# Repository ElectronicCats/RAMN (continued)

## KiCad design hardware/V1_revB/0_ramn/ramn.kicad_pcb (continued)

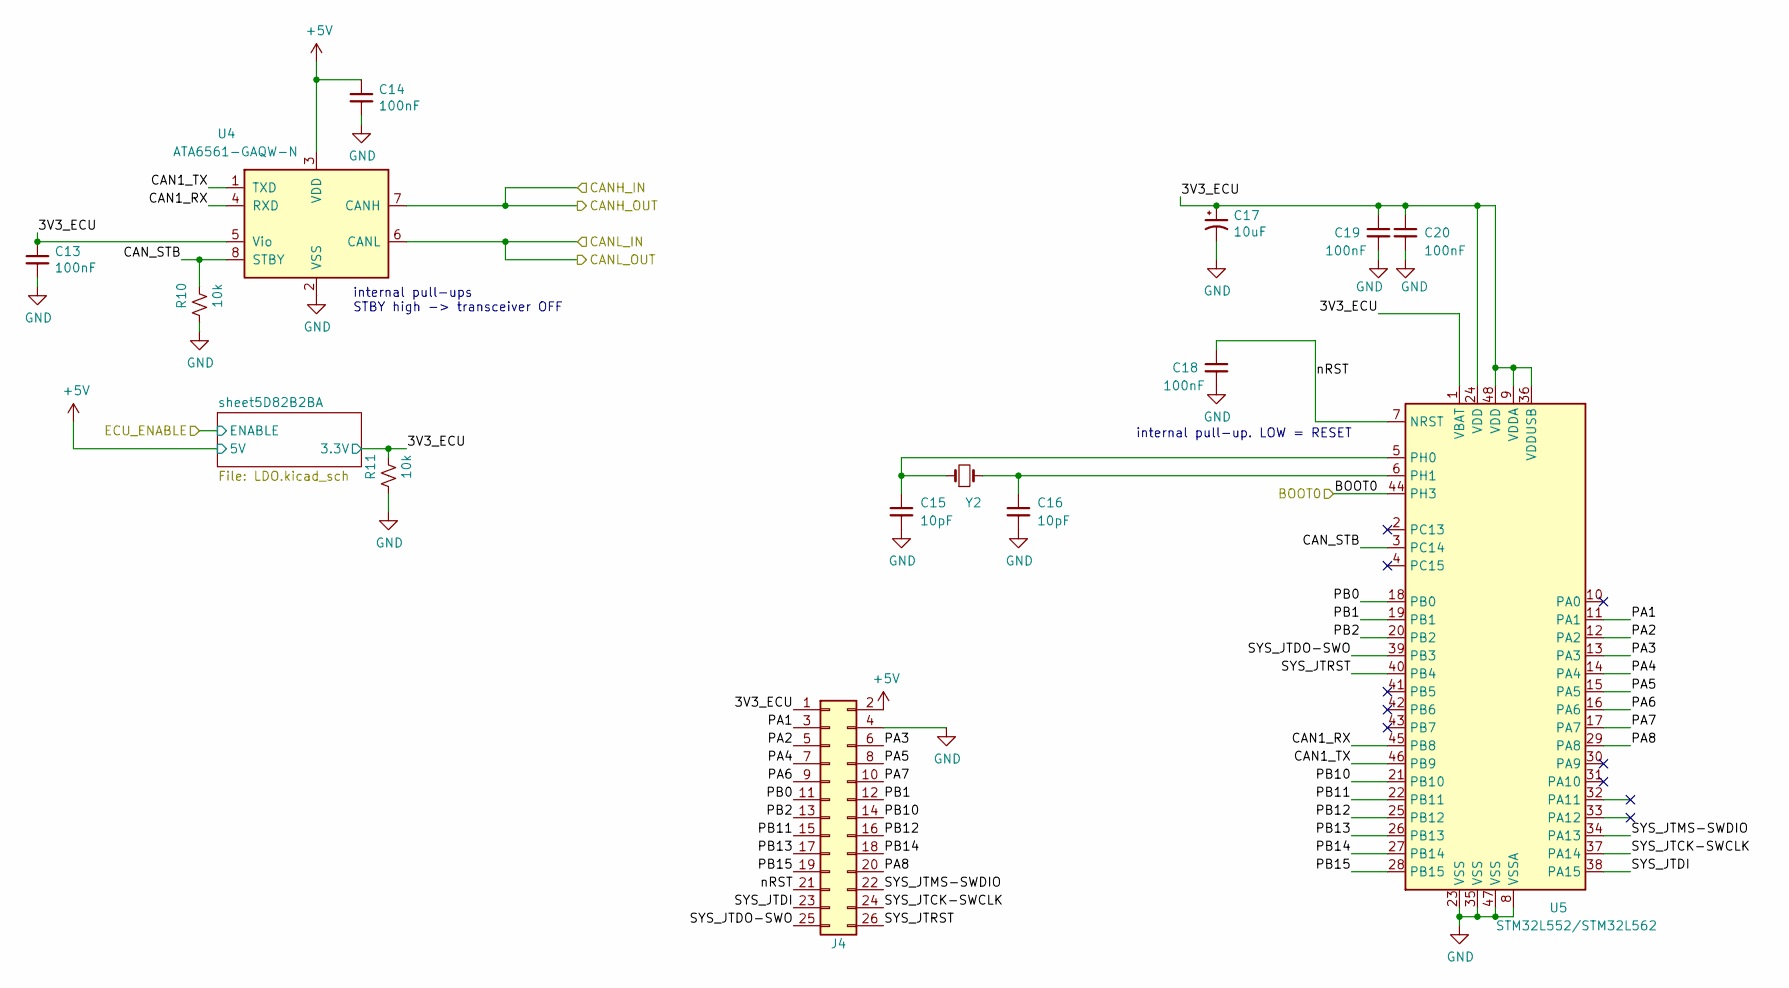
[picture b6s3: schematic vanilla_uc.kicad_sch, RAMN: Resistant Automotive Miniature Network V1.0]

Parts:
C13, C14, C18, C19, C20: 100nF; C_0603_1608Metric; lcsc# C599645
C15, C16: 10pF; C_0603_1608Metric; lcsc# C9807
C17: 10uF; C_1206_3216Metric; lcsc# C1848
J4: PinSocket_2x13_P2.54mm_Vertical; lcsc# C2897414
R10, R11: 10k; R_0603_1608Metric; lcsc# C98220
U4: ATA6561-GAQW-N; SOIC-8_3.9x4.9mm_P1.27mm; lcsc# C124015
U5: STM32L552/STM32L562; LQFP-48_7x7mm_P0.5mm; lcsc# C2969980
Y2: NX3225GD-8MHZ-STD-CRA-3; SMD-2_3.2x2.5mm; lcsc# C889706

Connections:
+5V: C14.1, J4.2, U4.3 (VDD); also elsewhere on the board
/ECUB/3V3_ECU: C13.1, C17.1, C19.1, C20.1, J4.1, R11.1, U4.5 (Vio), U5.1 (VBAT), U5.9 (VDDA), U5.24 (VDD), U5.36 (VDDUSB), U5.48 (VDD); also elsewhere on the board
/ECUB/BOOT0: U5.44 (PH3); also elsewhere on the board
/ECUB/CAN1_RX: U4.4 (RXD), U5.45 (PB8)
/ECUB/CAN1_TX: U4.1 (TXD), U5.46 (PB9)
/ECUB/CANH_IN: U4.7 (CANH); also elsewhere on the board
/ECUB/CANL_IN: U4.6 (CANL); also elsewhere on the board
/ECUB/CAN_STB: R10.1, U4.8 (STBY), U5.3 (PC14)
/ECUB/PA1: J4.3, U5.11 (PA1)
/ECUB/PA2: J4.5, U5.12 (PA2)
/ECUB/PA3: J4.6, U5.13 (PA3)
/ECUB/PA4: J4.7, U5.14 (PA4)
/ECUB/PA5: J4.8, U5.15 (PA5)
/ECUB/PA6: J4.9, U5.16 (PA6)
/ECUB/PA7: J4.10, U5.17 (PA7)
/ECUB/PA8: J4.20, U5.29 (PA8)
/ECUB/PB0: J4.11, U5.18 (PB0)
/ECUB/PB1: J4.12, U5.19 (PB1)
/ECUB/PB2: J4.13, U5.20 (PB2)
/ECUB/PB10: J4.14, U5.21 (PB10)
/ECUB/PB11: J4.15, U5.22 (PB11)
/ECUB/PB12: J4.16, U5.25 (PB12)
/ECUB/PB13: J4.17, U5.26 (PB13)
/ECUB/PB14: J4.18, U5.27 (PB14)
/ECUB/PB15: J4.19, U5.28 (PB15)
/ECUB/SYS_JTCK-SWCLK: J4.24, U5.37 (PA14)
/ECUB/SYS_JTDI: J4.23, U5.38 (PA15)
/ECUB/SYS_JTDO-SWO: J4.25, U5.39 (PB3)
/ECUB/SYS_JTMS-SWDIO: J4.22, U5.34 (PA13)
/ECUB/SYS_JTRST: J4.26, U5.40 (PB4)
/ECUB/nRST: C18.1, J4.21, U5.7 (NRST)
GND: C13.2, C14.2, C15.2, C16.2, C17.2, C18.2, C19.2, C20.2, J4.4, R10.2, R11.2, U4.2 (VSS), U5.8 (VSSA), U5.23 (VSS), U5.35 (VSS), U5.47 (VSS); also elsewhere on the board
unnamed: C15.1, U5.5 (PH0), Y2.1
unnamed: C16.1, U5.6 (PH1), Y2.2

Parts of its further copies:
C23, C24, C28, C29, C30: 100nF; C_0603_1608Metric; lcsc# C599645
C25, C26: 10pF; C_0603_1608Metric; lcsc# C9807
C27: 10uF; C_1206_3216Metric; lcsc# C1848
J5: PinSocket_2x13_P2.54mm_Vertical; lcsc# C2897414
R12, R13: 10k; R_0603_1608Metric; lcsc# C98220
U7: ATA6561-GAQW-N; SOIC-8_3.9x4.9mm_P1.27mm; lcsc# C124015
U8: STM32L552/STM32L562; LQFP-48_7x7mm_P0.5mm; lcsc# C2969980
Y3: NX3225GD-8MHZ-STD-CRA-3; SMD-2_3.2x2.5mm; lcsc# C889706

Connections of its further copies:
+5V: C24.1, J5.2, U7.3 (VDD); also elsewhere on the board
/ECUB/CANH_IN: U7.7 (CANH); also elsewhere on the board
/ECUB/CANL_IN: U7.6 (CANL); also elsewhere on the board
/ECUC/3V3_ECU: C23.1, C27.1, C29.1, C30.1, J5.1, R13.1, U7.5 (Vio), U8.1 (VBAT), U8.9 (VDDA), U8.24 (VDD), U8.36 (VDDUSB), U8.48 (VDD); also elsewhere on the board
/ECUC/BOOT0: U8.44 (PH3); also elsewhere on the board
/ECUC/CAN1_RX: U7.4 (RXD), U8.45 (PB8)
/ECUC/CAN1_TX: U7.1 (TXD), U8.46 (PB9)
/ECUC/CAN_STB: R12.1, U7.8 (STBY), U8.3 (PC14)
/ECUC/PA1: J5.3, U8.11 (PA1)
/ECUC/PA2: J5.5, U8.12 (PA2)
/ECUC/PA3: J5.6, U8.13 (PA3)
/ECUC/PA4: J5.7, U8.14 (PA4)
/ECUC/PA5: J5.8, U8.15 (PA5)
/ECUC/PA6: J5.9, U8.16 (PA6)
/ECUC/PA7: J5.10, U8.17 (PA7)
/ECUC/PA8: J5.20, U8.29 (PA8)
/ECUC/PB0: J5.11, U8.18 (PB0)
/ECUC/PB1: J5.12, U8.19 (PB1)
/ECUC/PB2: J5.13, U8.20 (PB2)
/ECUC/PB10: J5.14, U8.21 (PB10)
/ECUC/PB11: J5.15, U8.22 (PB11)
/ECUC/PB12: J5.16, U8.25 (PB12)
/ECUC/PB13: J5.17, U8.26 (PB13)
/ECUC/PB14: J5.18, U8.27 (PB14)
/ECUC/PB15: J5.19, U8.28 (PB15)
/ECUC/SYS_JTCK-SWCLK: J5.24, U8.37 (PA14)
/ECUC/SYS_JTDI: J5.23, U8.38 (PA15)
/ECUC/SYS_JTDO-SWO: J5.25, U8.39 (PB3)
/ECUC/SYS_JTMS-SWDIO: J5.22, U8.34 (PA13)
/ECUC/SYS_JTRST: J5.26, U8.40 (PB4)
/ECUC/nRST: C28.1, J5.21, U8.7 (NRST)
GND: C23.2, C24.2, C25.2, C26.2, C27.2, C28.2, C29.2, C30.2, J5.4, R12.2, R13.2, U7.2 (VSS), U8.8 (VSSA), U8.23 (VSS), U8.35 (VSS), U8.47 (VSS); also elsewhere on the board
unnamed: C25.1, U8.5 (PH0), Y3.1
unnamed: C26.1, U8.6 (PH1), Y3.2

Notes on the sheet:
internal pull-up. LOW = RESET
internal pull-ups STBY high -> transceiver OFF

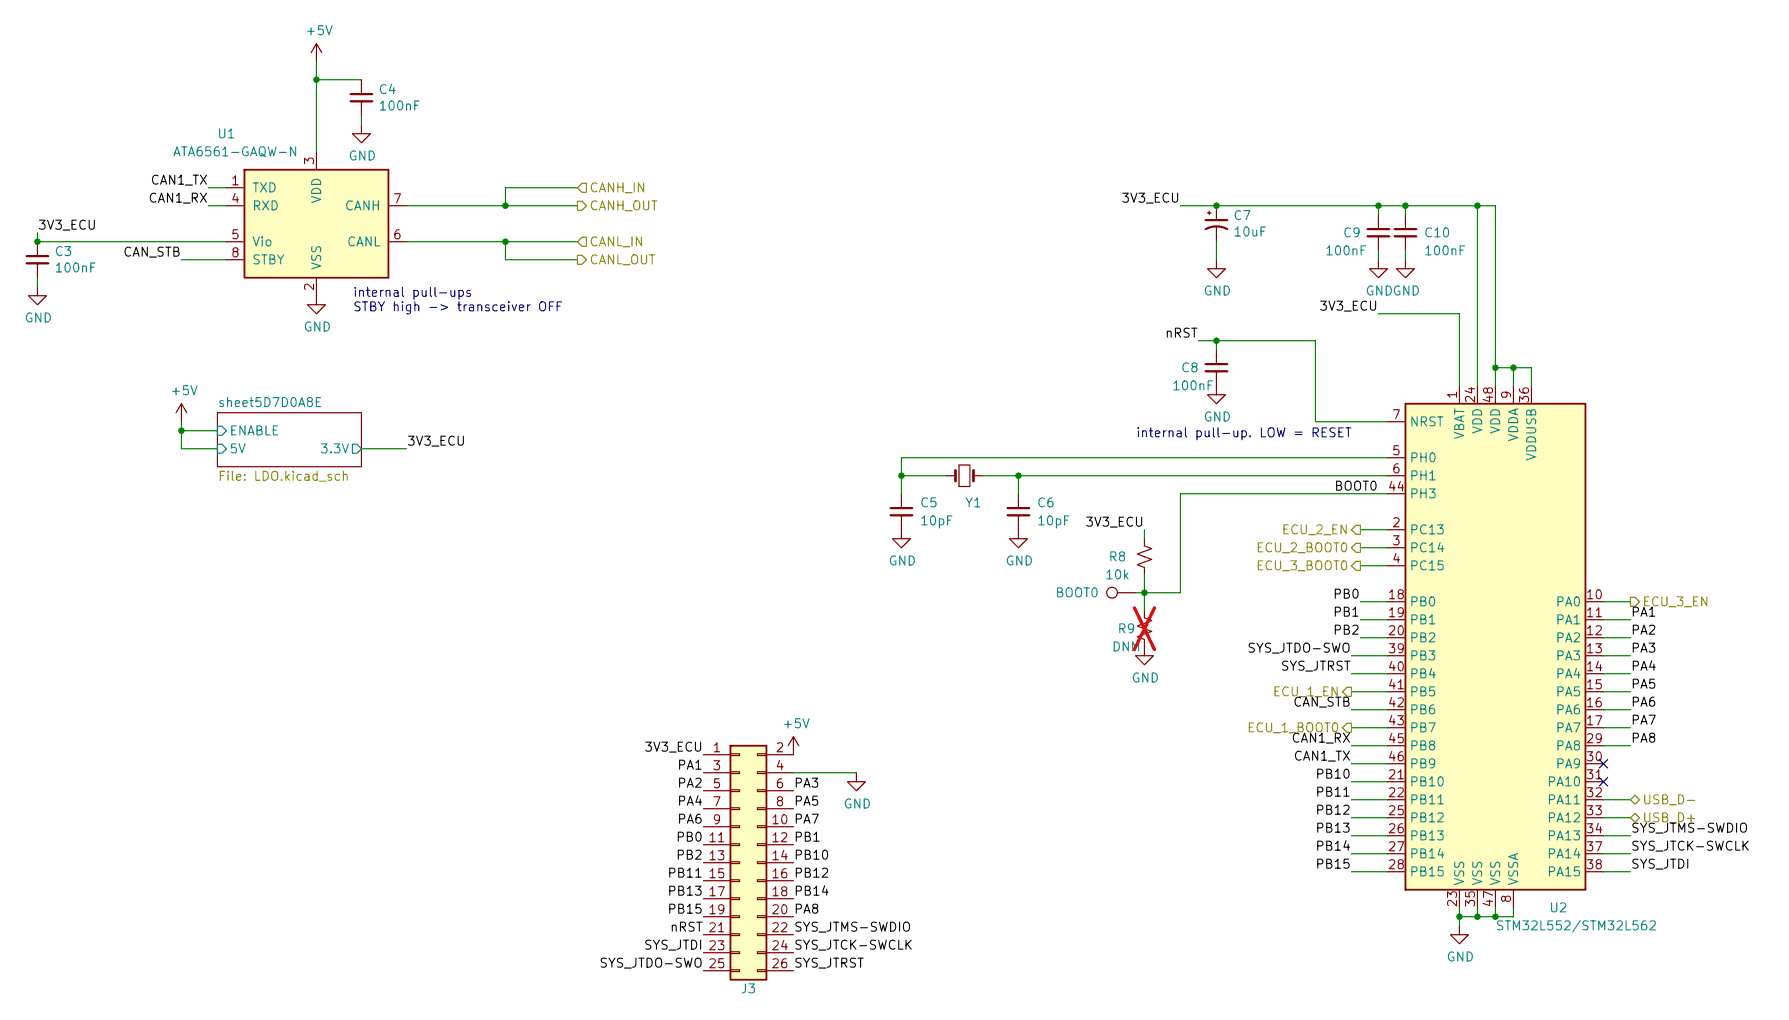
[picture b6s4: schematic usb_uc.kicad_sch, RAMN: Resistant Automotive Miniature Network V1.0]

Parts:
BOOT0: TestPoint_Pad_D1.0mm; lcsc# C5277086
C3, C4, C8, C9, C10: 100nF; C_0603_1608Metric; lcsc# C599645
C5, C6: 10pF; C_0603_1608Metric; lcsc# C9807
C7: 10uF; C_1206_3216Metric; lcsc# C1848
J3: PinSocket_2x13_P2.54mm_Vertical; lcsc# C2897414
R8: 10k; R_0603_1608Metric; lcsc# C98220
R9: DNM; R_0603_1608Metric; not fitted
U1: ATA6561-GAQW-N; SOIC-8_3.9x4.9mm_P1.27mm; lcsc# C124015
U2: STM32L552/STM32L562; LQFP-48_7x7mm_P0.5mm; lcsc# C2969980
Y1: NX3225GD-8MHZ-STD-CRA-3; SMD-2_3.2x2.5mm; lcsc# C889706

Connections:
+5V: C4.1, J3.2, U1.3 (VDD); also elsewhere on the board
/ECUB/BOOT0: U2.43 (PB7); also elsewhere on the board
/ECUB/CANH_IN: U1.7 (CANH); also elsewhere on the board
/ECUB/CANL_IN: U1.6 (CANL); also elsewhere on the board
/ECUB/ECU_ENABLE: U2.41 (PB5); also elsewhere on the board
/ECUC/BOOT0: U2.3 (PC14); also elsewhere on the board
/ECUC/ECU_ENABLE: U2.2 (PC13); also elsewhere on the board
/ECUD/BOOT0: U2.4 (PC15); also elsewhere on the board
/ECUD/ECU_ENABLE: U2.10 (PA0); also elsewhere on the board
/usb_uc/3V3_ECU: C3.1, C7.1, C9.1, C10.1, J3.1, R8.1, U1.5 (Vio), U2.1 (VBAT), U2.9 (VDDA), U2.24 (VDD), U2.36 (VDDUSB), U2.48 (VDD); also elsewhere on the board
/usb_uc/BOOT0: BOOT0.1 (1_1), R8.2, R9.1, U2.44 (PH3)
/usb_uc/CAN1_RX: U1.4 (RXD), U2.45 (PB8)
/usb_uc/CAN1_TX: U1.1 (TXD), U2.46 (PB9)
/usb_uc/CAN_STB: U1.8 (STBY), U2.42 (PB6)
/usb_uc/PA1: J3.3, U2.11 (PA1)
/usb_uc/PA2: J3.5, U2.12 (PA2)
/usb_uc/PA3: J3.6, U2.13 (PA3)
/usb_uc/PA4: J3.7, U2.14 (PA4)
/usb_uc/PA5: J3.8, U2.15 (PA5)
/usb_uc/PA6: J3.9, U2.16 (PA6)
/usb_uc/PA7: J3.10, U2.17 (PA7)
/usb_uc/PA8: J3.20, U2.29 (PA8)
/usb_uc/PB0: J3.11, U2.18 (PB0)
/usb_uc/PB1: J3.12, U2.19 (PB1)
/usb_uc/PB2: J3.13, U2.20 (PB2)
/usb_uc/PB10: J3.14, U2.21 (PB10)
/usb_uc/PB11: J3.15, U2.22 (PB11)
/usb_uc/PB12: J3.16, U2.25 (PB12)
/usb_uc/PB13: J3.17, U2.26 (PB13)
/usb_uc/PB14: J3.18, U2.27 (PB14)
/usb_uc/PB15: J3.19, U2.28 (PB15)
/usb_uc/SYS_JTCK-SWCLK: J3.24, U2.37 (PA14)
/usb_uc/SYS_JTDI: J3.23, U2.38 (PA15)
/usb_uc/SYS_JTDO-SWO: J3.25, U2.39 (PB3)
/usb_uc/SYS_JTMS-SWDIO: J3.22, U2.34 (PA13)
/usb_uc/SYS_JTRST: J3.26, U2.40 (PB4)
/usb_uc/USB_D+: U2.33 (PA12); also elsewhere on the board
/usb_uc/USB_D-: U2.32 (PA11); also elsewhere on the board
/usb_uc/nRST: C8.1, J3.21, U2.7 (NRST)
GND: C3.2, C4.2, C5.2, C6.2, C7.2, C8.2, C9.2, C10.2, J3.4, R9.2, U1.2 (VSS), U2.8 (VSSA), U2.23 (VSS), U2.35 (VSS), U2.47 (VSS); also elsewhere on the board
unnamed: C5.1, U2.5 (PH0), Y1.1
unnamed: C6.1, U2.6 (PH1), Y1.2

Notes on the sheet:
internal pull-up. LOW = RESET
internal pull-ups STBY high -> transceiver OFF

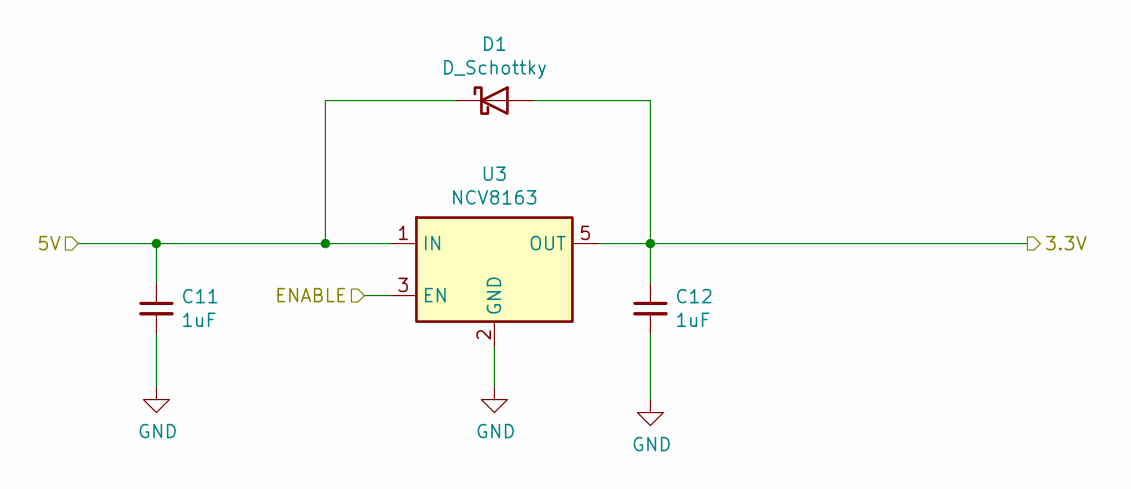
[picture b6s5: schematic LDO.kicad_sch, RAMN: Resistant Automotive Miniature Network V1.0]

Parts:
C11, C12: 1uF; C_1206_3216Metric; lcsc# C90539
D1: D_Schottky; D_SOD-523; lcsc# C154821
U3: NCV8163; TSOP-5_1.65x3.05mm_P0.95mm; lcsc# C604041

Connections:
+5V: C11.1, D1.1 (K), U3.1 (IN), U3.3 (EN); also elsewhere on the board
/usb_uc/3V3_ECU: C12.1, D1.2 (A), U3.5 (OUT); also elsewhere on the board
GND: C11.2, C12.2, U3.2 (GND); also elsewhere on the board

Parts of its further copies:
C21, C22, C31, C32, C41, C42: 1uF; C_1206_3216Metric; lcsc# C90539
D2, D3, D4: D_Schottky; D_SOD-523; lcsc# C154821
U6, U9, U12: NCV8163; TSOP-5_1.65x3.05mm_P0.95mm; lcsc# C604041

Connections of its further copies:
+5V: C21.1, C31.1, C41.1, D2.1 (K), D3.1 (K), D4.1 (K), U6.1 (IN), U9.1 (IN), U12.1 (IN); also elsewhere on the board
/ECUB/3V3_ECU: C22.1, D2.2 (A), U6.5 (OUT); also elsewhere on the board
/ECUB/ECU_ENABLE: U6.3 (EN); also elsewhere on the board
/ECUC/3V3_ECU: C32.1, D3.2 (A), U9.5 (OUT); also elsewhere on the board
/ECUC/ECU_ENABLE: U9.3 (EN); also elsewhere on the board
/ECUD/ECU_ENABLE: U12.3 (EN); also elsewhere on the board
/ECUD/sheet5D7F273B/3.3V: C42.1, D4.2 (A), U12.5 (OUT); also elsewhere on the board
GND: C21.2, C22.2, C31.2, C32.2, C41.2, C42.2, U6.2 (GND), U9.2 (GND), U12.2 (GND); also elsewhere on the board

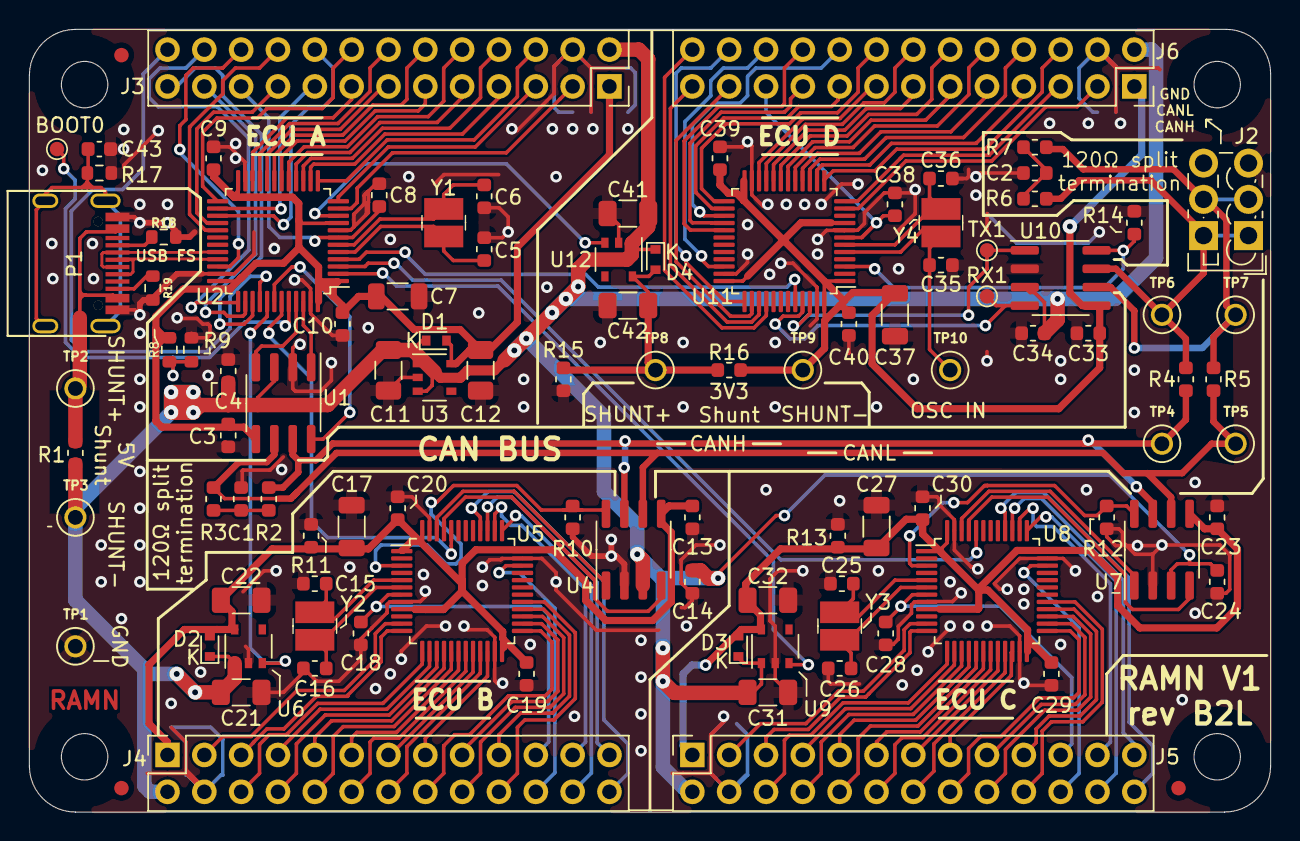
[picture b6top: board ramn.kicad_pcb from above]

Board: 2 copper layers, 85.6 x 54.0 mm, 108 parts (0 on the bottom side), 138 nets.

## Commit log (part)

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2024-08-29 feat (hw): change USB to USB C and change Test points footprints
2024-08-29 chore: update gitignore
2024-08-29 fix (hw): update Test point footprint
2024-08-29 feat: test points in body got changed
2024-08-29 feat: debugger test points changed
2024-08-30 feat: potentiometer footprint changed
2024-09-01 fix: update files
